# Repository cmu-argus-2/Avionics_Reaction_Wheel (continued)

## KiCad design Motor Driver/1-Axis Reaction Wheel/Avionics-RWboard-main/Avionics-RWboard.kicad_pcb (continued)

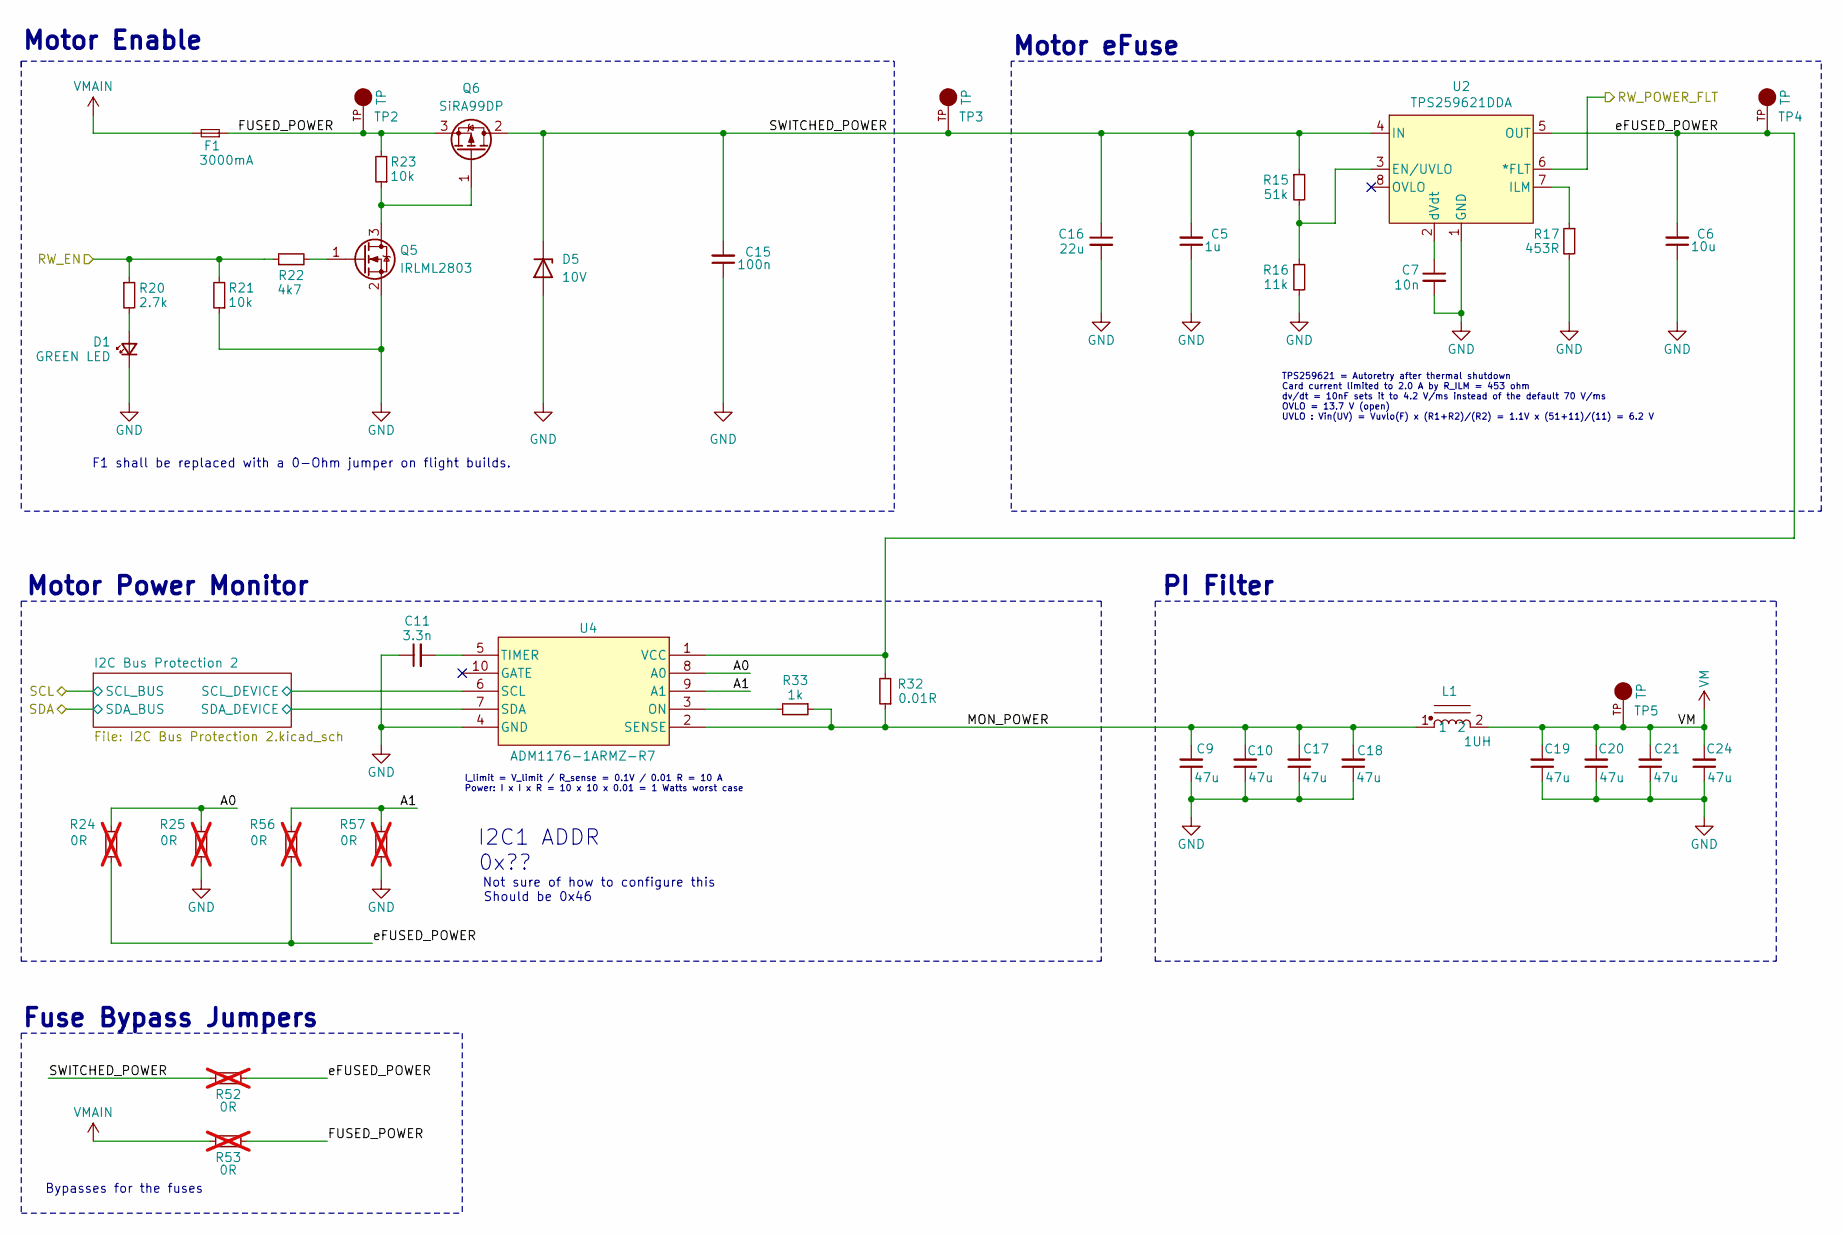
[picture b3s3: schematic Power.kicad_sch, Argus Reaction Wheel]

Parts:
C5: 1u; C_0603_1608Metric; Part CL10B105KA8NNNC; Digikey PN 1276-1184-1-ND
C6: 10u; C_1206_3216Metric_Pad1.33x1.80mm_HandSolder; Part CL31B106KAHNNNE; Digikey PN 1276-1804-1-ND
C7: 10n; C_0603_1608Metric; MPN CL10B103KO8WPNC; Digikey PN 490-4934-1-ND
C9, C10, C17, C18, C19, C20, C21, C24: 47u; C_1206_3216Metric_Pad1.33x1.80mm_HandSolder; Part C3216X5R1E476M160AC; Digikey PN 445-8047-1-ND
C11: 3.3n; C_0603_1608Metric; Part C0603C332K4REC7411; Digikey PN 399-C0603C332K4REC7411CT-ND
C15: 100n; C_0402_1005Metric_Pad0.74x0.62mm_HandSolder; Part C0402C103K3RACTU; Digikey PN 399-C0402C103K3RACTUCT-ND
C16: 22u; C_1210_3225Metric_Pad1.33x2.70mm_HandSolder; MPN GCM32EC71E226KE36K; Digikey PN 490-GCM32EC71E226KE36KCT-ND
D1: GREEN LED; LED_0603_1608Metric; MPN IN-S63AT5A; Digikey PN 1830-1064-1-ND
D5: 10V; Nexperia_DSN1608-2_1.6x0.8mm; MPN PTVS10VZ1USKYL; Digikey PN 1727-2744-1-ND
F1: 3000mA; Fuse_0603_1608Metric; Part SF-0603S300-2; Digikey PN SF-0603S300-2CT-ND
L1: 1UH; HCM1A1104V2; Part HCM1A1104V2-1R0-R; Digikey PN 283-HCM1A1104V2-1R0-RCT-ND
Q5: IRLML2803; SOT-23; MPN IRLML2803TRPBF; Digikey PN IRLML2803PBFCT-ND
Q6: SiRA99DP; PowerPAK SO-8; MPN SIRA99DP-T1-GE3; Digikey PN SIRA99DP-T1-GE3CT-ND
R15: 51k; R_0603_1608Metric; MPN RC0603FR-0751KL; Digikey PN 311-51.0KHRCT-ND
R16: 11k; R_0603_1608Metric; MPN RC0603FR-0711KL; Digikey PN 311-11.0KHRCT-ND
R17: 453R; R_0603_1608Metric; MPN RC0603FR-07453RL; Digikey PN 311-453HRCT-ND
R20: 2.7k; R_0603_1608Metric; MPN CRGCQ0603F2K7; Digikey PN A129693CT-ND
R21, R23: 10k; R_0603_1608Metric; MPN RC0603FR-0710KL; Digikey PN 311-10.0KHRCT-ND
R22: 4k7; R_0603_1608Metric; MPN RC0603FR-074K7L; Digikey PN 311-4.70KHRCT-ND
R24, R25, R56, R57: 0R; R_0402_1005Metric_Pad0.72x0.64mm_HandSolder; MPN RC0402JR-070RL; Digikey PN 311-0.0JRCT-ND; not fitted
R32: 0.01R; R_0805_2012Metric_Pad1.20x1.40mm_HandSolder; Part ERJ-8BWFR010V; Digikey PN P.010AUCT-ND
R33: 1k; R_0603_1608Metric; MPN RC0603FR-071KL; Digikey PN 311-1.00KHRCT-ND
R52, R53: 0R; R_2512_6332Metric_Pad1.40x3.35mm_HandSolder; Part RC2512FK-070RL; Digikey PN 13-RC2512FK-070RLCT-ND; not fitted
TP2, TP3, TP4, TP5: TP; KEYSTONE_5001; MPN 5001; Digikey PN 36-5001-ND
U2: TPS259621DDA; Texas_R-PDSO-G8_EP2.95x4.9mm_Mask2.4x3.1mm_ThermalVias; MPN TPS259620DDAT; Digikey PN 296-TPS259621DDARCT-ND
U4: ADM1176-1ARMZ-R7; MSOP-10_3x3mm_P0.5mm; Manufacturer_Part_Number ADM1176-1ARMZ-R7; Digikey PN 505-ADM1176-1ARMZ-R7CT-ND

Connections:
/Connectors/RW_EN: R20.1, R21.2, R22.1; also elsewhere on the board
/Connectors/RW_POWER_FLT: U2.6 (*FLT); also elsewhere on the board
/Power/A0: R24.2, R25.2, U4.8 (A0)
/Power/A1: R56.2, R57.2, U4.9 (A1)
/Power/FUSED_POWER: F1.1, Q6.3 (S), R23.2, R53.1, TP2.TP
/Power/I2C Bus Protection 2/SCL_DEVICE: U4.6 (SCL); also elsewhere on the board
/Power/I2C Bus Protection 2/SDA_DEVICE: U4.7 (SDA); also elsewhere on the board
/Power/MON_POWER: C9.2, C10.2, C17.2, C18.2, L1.1, R32.1, R33.1, U4.2 (SENSE)
/Power/SWITCHED_POWER: C5.2, C15.2, C16.1, D5.1 (K), Q6.2 (D), R15.1, R52.2, TP3.TP, U2.4 (IN)
/Power/eFUSED_POWER: C6.2, R24.1, R32.2, R52.1, R56.1, TP4.TP, U2.5 (OUT), U4.1 (VCC)
GND: C5.1, C6.1, C7.2, C9.1, C10.1, C11.1, C15.1, C16.2, C17.1, C18.1, C19.1, C20.1, C21.1, C24.1, D1.1 (K), D5.2 (A), Q5.2 (S), R16.2, R17.2, R21.1, R25.1, R57.1, U2.1 (GND), U2.9 (GND), U4.4 (GND); also elsewhere on the board
unnamed: D1.2 (A), R20.2
unnamed: Q5.3 (D), Q6.1 (G), R23.1
unnamed: Q5.1 (G), R22.2
unnamed: R15.2, R16.1, U2.3 (EN/UVLO)
unnamed: R17.1, U2.7 (ILM)
unnamed: C7.1, U2.2 (dVdt)
unnamed: R33.2, U4.3 (ON)
unnamed: C11.2, U4.5 (TIMER)
VM: C19.2, C20.2, C21.2, C24.2, L1.2, TP5.TP; also elsewhere on the board
VMAIN: F1.2, R53.2; also elsewhere on the board

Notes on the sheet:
Not sure of how to configure this
I2C1 ADDR
0x??
Motor Enable
F1 shall be replaced with a 0-Ohm jumper on flight builds.
I_limit = V_limit / R_sense = 0.1V / 0.01 R = 10 A Power: I x I x R = 10 x 10 x 0.01 = 1 Watts worst case
Motor Power Monitor
TPS259621 = Autoretry after thermal shutdown Card current limited to 2.0 A by R_ILM = 453 ohm dv/dt = 10nF sets it to 4.2 V/ms instead of the default 70 V/ms OVLO = 13.7 V (open) UVLO : Vin(UV) = Vuvlo(F) x (R1+R2)/(R2) = 1.1V x (51+11)/(11) = 6.2 V
Fuse Bypass Jumpers
Should be 0x46
PI Filter
Bypasses for the fuses
Motor eFuse

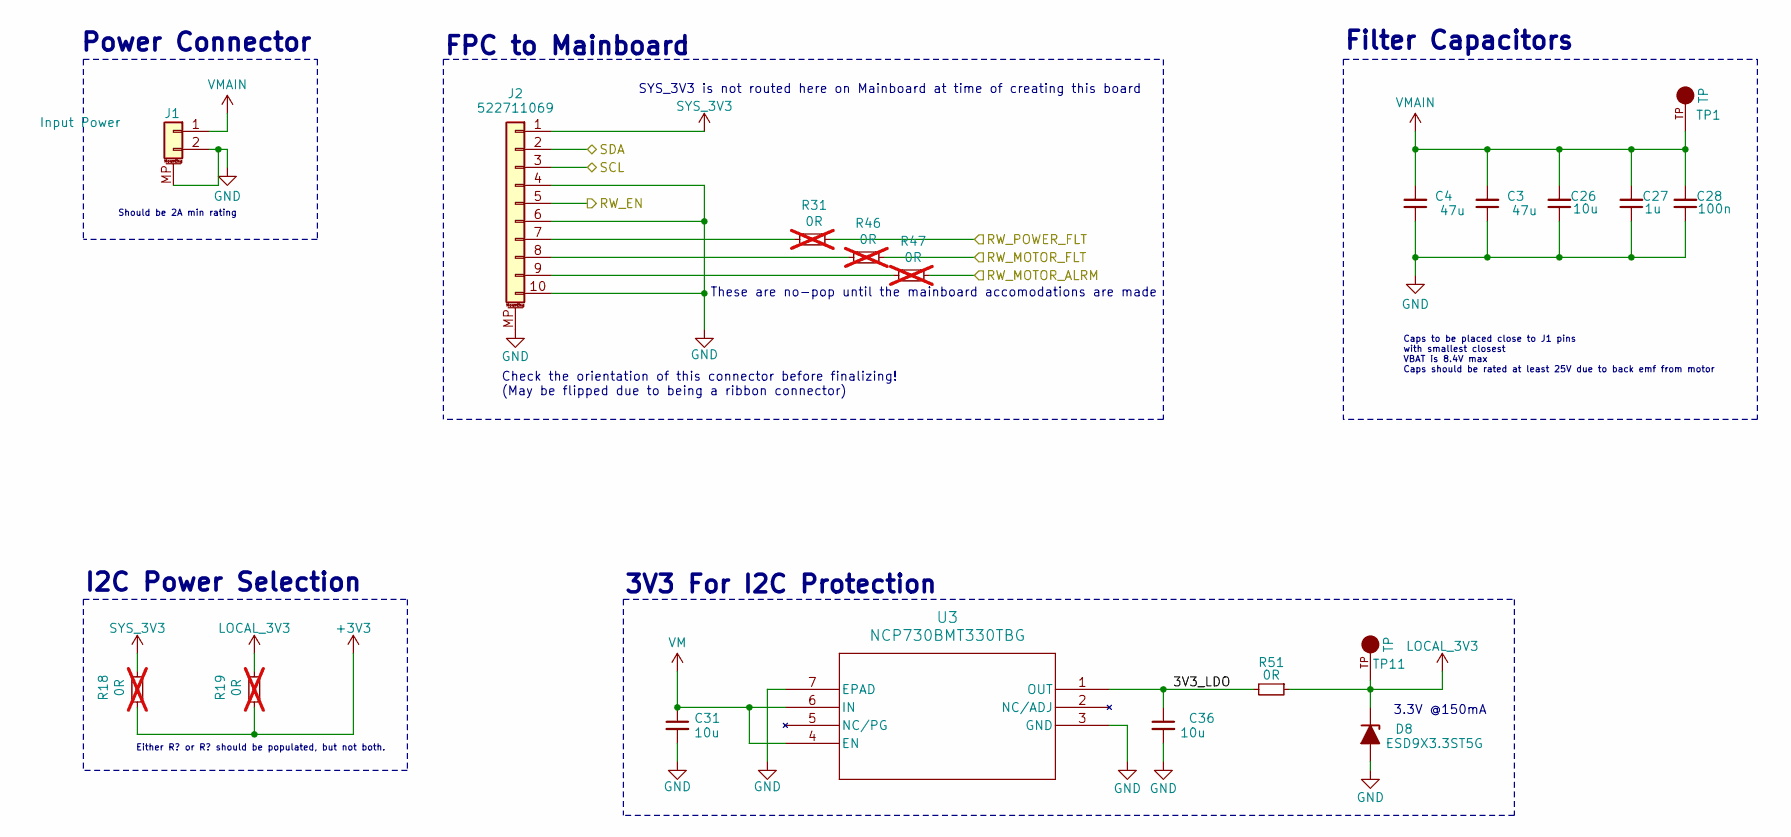
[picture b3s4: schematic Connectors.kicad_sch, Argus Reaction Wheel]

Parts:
C3, C4: 47u; C_1206_3216Metric_Pad1.33x1.80mm_HandSolder; Part C3216X5R1E476M160AC; Digikey PN 445-8047-1-ND
C26: 10u; C_1206_3216Metric_Pad1.33x1.80mm_HandSolder; Part CL31B106KAHNNNE; Digikey PN 1276-1804-1-ND
C27: 1u; C_0603_1608Metric; Part CL10B105KA8NNNC; Digikey PN 1276-1184-1-ND
C28: 100n; C_0402_1005Metric_Pad0.74x0.62mm_HandSolder; Part C0402C103K3RACTU; Digikey PN 399-C0402C103K3RACTUCT-ND
C31, C36: 10u; C_0603_1608Metric; MPN C1608X5R1E106M080AC; Digikey PN 445-9015-1-ND
D8: ESD9X3.3ST5G; D_SOD-923; MPN ESD9X5.0ST5G; Digikey PN ESD9X3.3ST5GOSCT-ND
J1: Input Power; Molex_Pico-Lock_504050-0291_1x02-1MP_P1.50mm_Horizontal
J2: 522711069; Molex_200528-0100_1x10-1MP_P1.00mm_Horizontal; MPN 200528-0100; Digikey PN 900-2005280100CT-ND
R18, R19, R31, R46, R47: 0R; R_0402_1005Metric_Pad0.72x0.64mm_HandSolder; MPN RC0402JR-070RL; Digikey PN 311-0.0JRCT-ND; not fitted
R51: 0R; R_0603_1608Metric; MPN CR0603-J/-000ELF; Digikey PN CR0603-J/-000ELFCT-ND
TP1, TP11: TP; KEYSTONE_5001; MPN 5001; Digikey PN 36-5001-ND
U3: NCP730BMT330TBG; WDFN6-2x2_511BR_OSI; MPN NCP730BMT330TBG; Digikey PN 488-NCP730BMT330TBGCT-ND

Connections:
+3V3: R18.1, R19.1; also elsewhere on the board
/Connectors/3V3_LDO: C36.1, R51.2, U3.1 (OUT)
/Connectors/RW_EN: J2.5; also elsewhere on the board
/Connectors/RW_MOTOR_ALRM: R47.2; also elsewhere on the board
/Connectors/RW_MOTOR_FLT: R46.2; also elsewhere on the board
/Connectors/RW_POWER_FLT: R31.2; also elsewhere on the board
/Connectors/SCL: J2.3; also elsewhere on the board
/Connectors/SDA: J2.2; also elsewhere on the board
GND: C3.1, C4.1, C26.1, C27.1, C28.1, C31.2, C36.2, D8.2 (A), J1.2, J1.MP (MountPin), J2.4, J2.6, J2.10, J2.MP (MountPin), U3.3 (GND), U3.7 (EPAD); also elsewhere on the board
LOCAL_3V3: D8.1 (K), R19.2, R51.1, TP11.TP
unnamed: J2.7, R31.1
unnamed: J2.8, R46.1
unnamed: J2.9, R47.1
SYS_3V3: J2.1, R18.2
VM: C31.1, U3.4 (EN), U3.6 (IN); also elsewhere on the board
VMAIN: C3.2, C4.2, C26.2, C27.2, C28.2, J1.1, TP1.TP; also elsewhere on the board

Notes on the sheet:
Filter Capacitors
Caps to be placed close to J1 pins with smallest closest VBAT is 8.4V max Caps should be rated at least 25V due to back emf from motor
3.3V @150mA
These are no-pop until the mainboard accomodations are made
Check the orientation of this connector before finalizing! (May be flipped due to being a ribbon connector)
Either R? or R? should be populated, but not both.
3V3 For I2C Protection
Should be 2A min rating
I2C Power Selection
SYS_3V3 is not routed here on Mainboard at time of creating this board
Power Connector
FPC to Mainboard

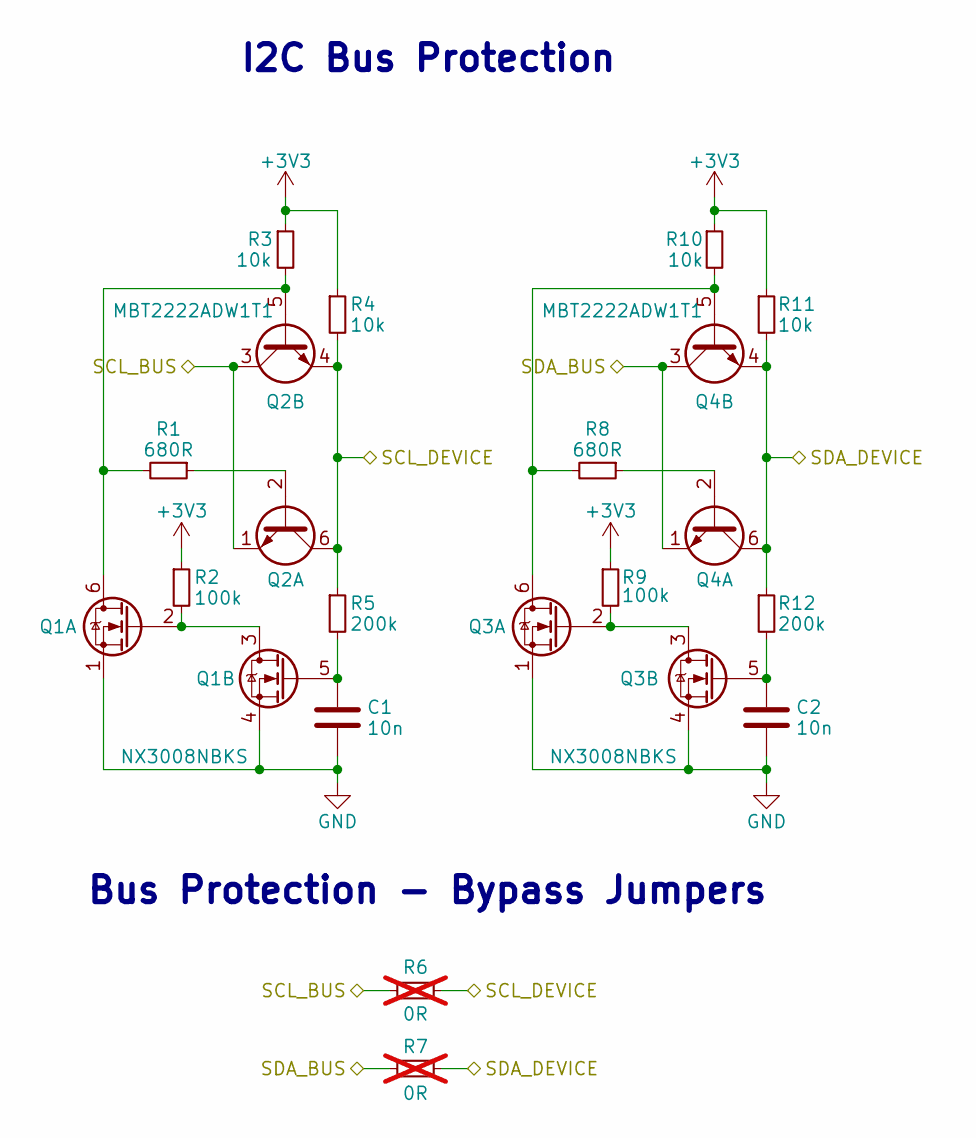
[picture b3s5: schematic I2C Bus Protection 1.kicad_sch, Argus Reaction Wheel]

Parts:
C1, C2: 10n; C_0603_1608Metric; Part CL10B103KO8WPNC; Digikey PN 490-4934-1-ND
Q1, Q3: NX3008NBKS; SOT-363_SC-70-6; Manufacturer_Part_Number NX3008NBKS; Digikey PN 1727-1221-1-ND
Q2, Q4: MBT2222ADW1T1; SOT-363_SC-70-6; Manufacturer_Part_Number MBT2222ADW1T1G; Digikey PN MBT2222ADW1T1GOSCT-ND
R1, R8: 680R; R_0603_1608Metric; MPN RC0603FR-07680RL; Digikey PN 311-680HRCT-ND
R2, R9: 100k; R_0603_1608Metric; MPN RC0603FR-07100KL; Digikey PN 311-100KHRCT-ND
R3, R4, R10, R11: 10k; R_0603_1608Metric; MPN RC0603FR-0710KL; Digikey PN 311-10.0KHRCT-ND
R5, R12: 200k; R_0603_1608Metric; MPN RC0603FR-07200KL; Digikey PN 311-200KHRCT-ND
R6, R7: 0R; R_0603_1608Metric; MPN CR0603-J/-000ELF; Digikey PN CR0603-J/-000ELFCT-ND; not fitted

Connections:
+3V3: R2.1, R3.1, R4.1, R9.1, R10.1, R11.1; also elsewhere on the board
/Connectors/SCL: Q2.1 (E1), Q2.3 (C2), R6.2; also elsewhere on the board
/Connectors/SDA: Q4.1 (E1), Q4.3 (C2), R7.2; also elsewhere on the board
/Motor/I2C Bus Protection 1/SCL_DEVICE: Q2.4 (E2), Q2.6 (C1), R4.2, R5.1, R6.1; also elsewhere on the board
/Motor/I2C Bus Protection 1/SDA_DEVICE: Q4.4 (E2), Q4.6 (C1), R7.1, R11.2, R12.1; also elsewhere on the board
GND: C1.2, C2.2, Q1.1 (S), Q1.4 (S), Q3.1 (S), Q3.4 (S); also elsewhere on the board
unnamed: Q1.6 (D), Q2.5 (B2), R1.2, R3.2
unnamed: Q1.2 (G), Q1.3 (D), R2.2
unnamed: C1.1, Q1.5 (G), R5.2
unnamed: Q2.2 (B1), R1.1
unnamed: Q3.6 (D), Q4.5 (B2), R8.2, R10.2
unnamed: Q3.2 (G), Q3.3 (D), R9.2
unnamed: C2.1, Q3.5 (G), R12.2
unnamed: Q4.2 (B1), R8.1

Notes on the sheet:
Bus Protection - Bypass Jumpers
I2C Bus Protection

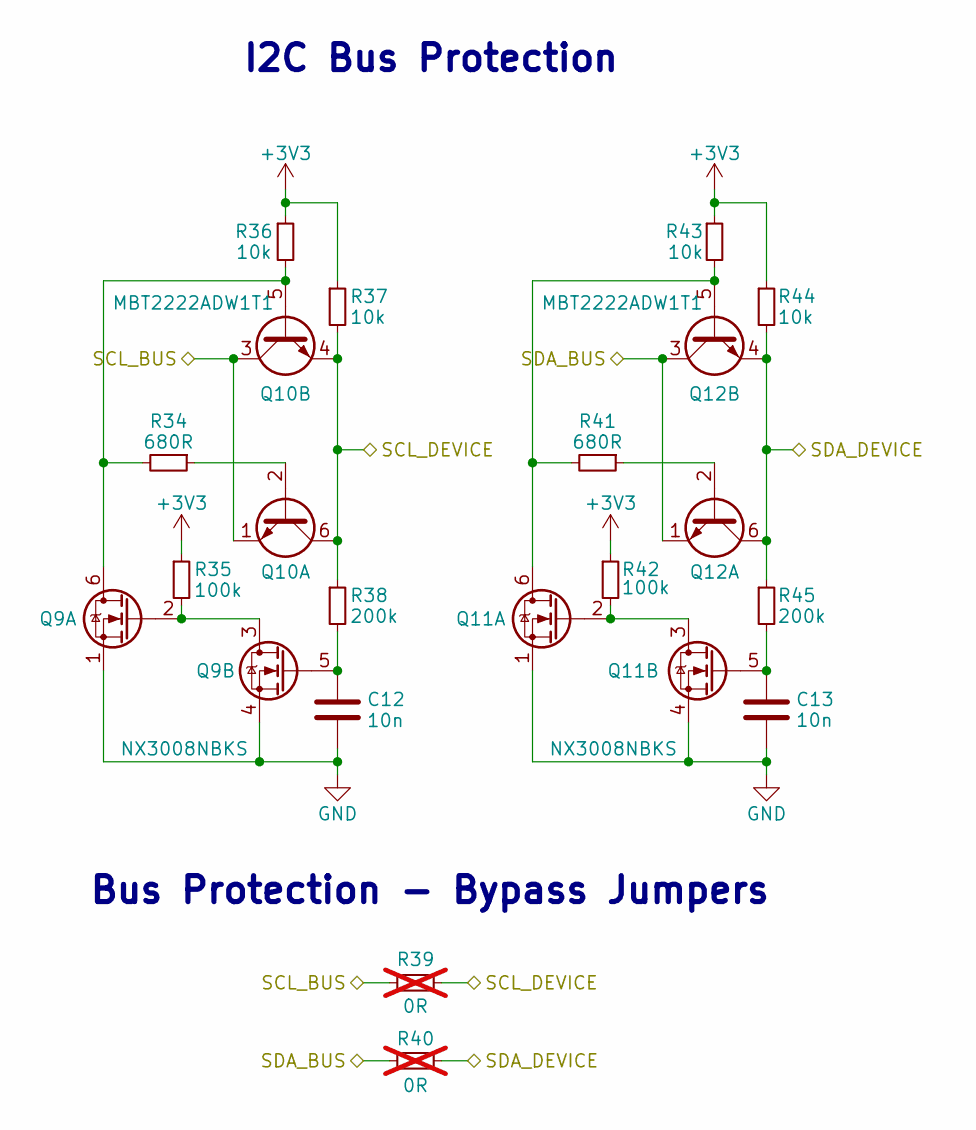
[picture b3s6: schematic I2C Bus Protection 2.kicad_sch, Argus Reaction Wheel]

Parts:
C12, C13: 10n; C_0603_1608Metric; Part CL10B103KO8WPNC; Digikey PN 490-4934-1-ND
Q9, Q11: NX3008NBKS; SOT-363_SC-70-6; Manufacturer_Part_Number NX3008NBKS; Digikey PN 1727-1221-1-ND
Q10, Q12: MBT2222ADW1T1; SOT-363_SC-70-6; Manufacturer_Part_Number MBT2222ADW1T1G; Digikey PN MBT2222ADW1T1GOSCT-ND
R34, R41: 680R; R_0603_1608Metric; MPN RC0603FR-07680RL; Digikey PN 311-680HRCT-ND
R35, R42: 100k; R_0603_1608Metric; MPN RC0603FR-07100KL; Digikey PN 311-100KHRCT-ND
R36, R37, R43, R44: 10k; R_0603_1608Metric; MPN RC0603FR-0710KL; Digikey PN 311-10.0KHRCT-ND
R38, R45: 200k; R_0603_1608Metric; MPN RC0603FR-07200KL; Digikey PN 311-200KHRCT-ND
R39, R40: 0R; R_0603_1608Metric; MPN CR0603-J/-000ELF; Digikey PN CR0603-J/-000ELFCT-ND; not fitted

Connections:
+3V3: R35.1, R36.1, R37.1, R42.1, R43.1, R44.1; also elsewhere on the board
/Connectors/SCL: Q10.1 (E1), Q10.3 (C2), R39.2; also elsewhere on the board
/Connectors/SDA: Q12.1 (E1), Q12.3 (C2), R40.2; also elsewhere on the board
/Power/I2C Bus Protection 2/SCL_DEVICE: Q10.4 (E2), Q10.6 (C1), R37.2, R38.1, R39.1; also elsewhere on the board
/Power/I2C Bus Protection 2/SDA_DEVICE: Q12.4 (E2), Q12.6 (C1), R40.1, R44.2, R45.1; also elsewhere on the board
GND: C12.2, C13.2, Q9.1 (S), Q9.4 (S), Q11.1 (S), Q11.4 (S); also elsewhere on the board
unnamed: Q9.2 (G), Q9.3 (D), R35.2
unnamed: C12.1, Q9.5 (G), R38.2
unnamed: Q10.2 (B1), R34.1
unnamed: Q9.6 (D), Q10.5 (B2), R34.2, R36.2
unnamed: Q11.6 (D), Q12.5 (B2), R41.2, R43.2
unnamed: Q11.2 (G), Q11.3 (D), R42.2
unnamed: C13.1, Q11.5 (G), R45.2
unnamed: Q12.2 (B1), R41.1

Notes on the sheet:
Bus Protection - Bypass Jumpers
I2C Bus Protection

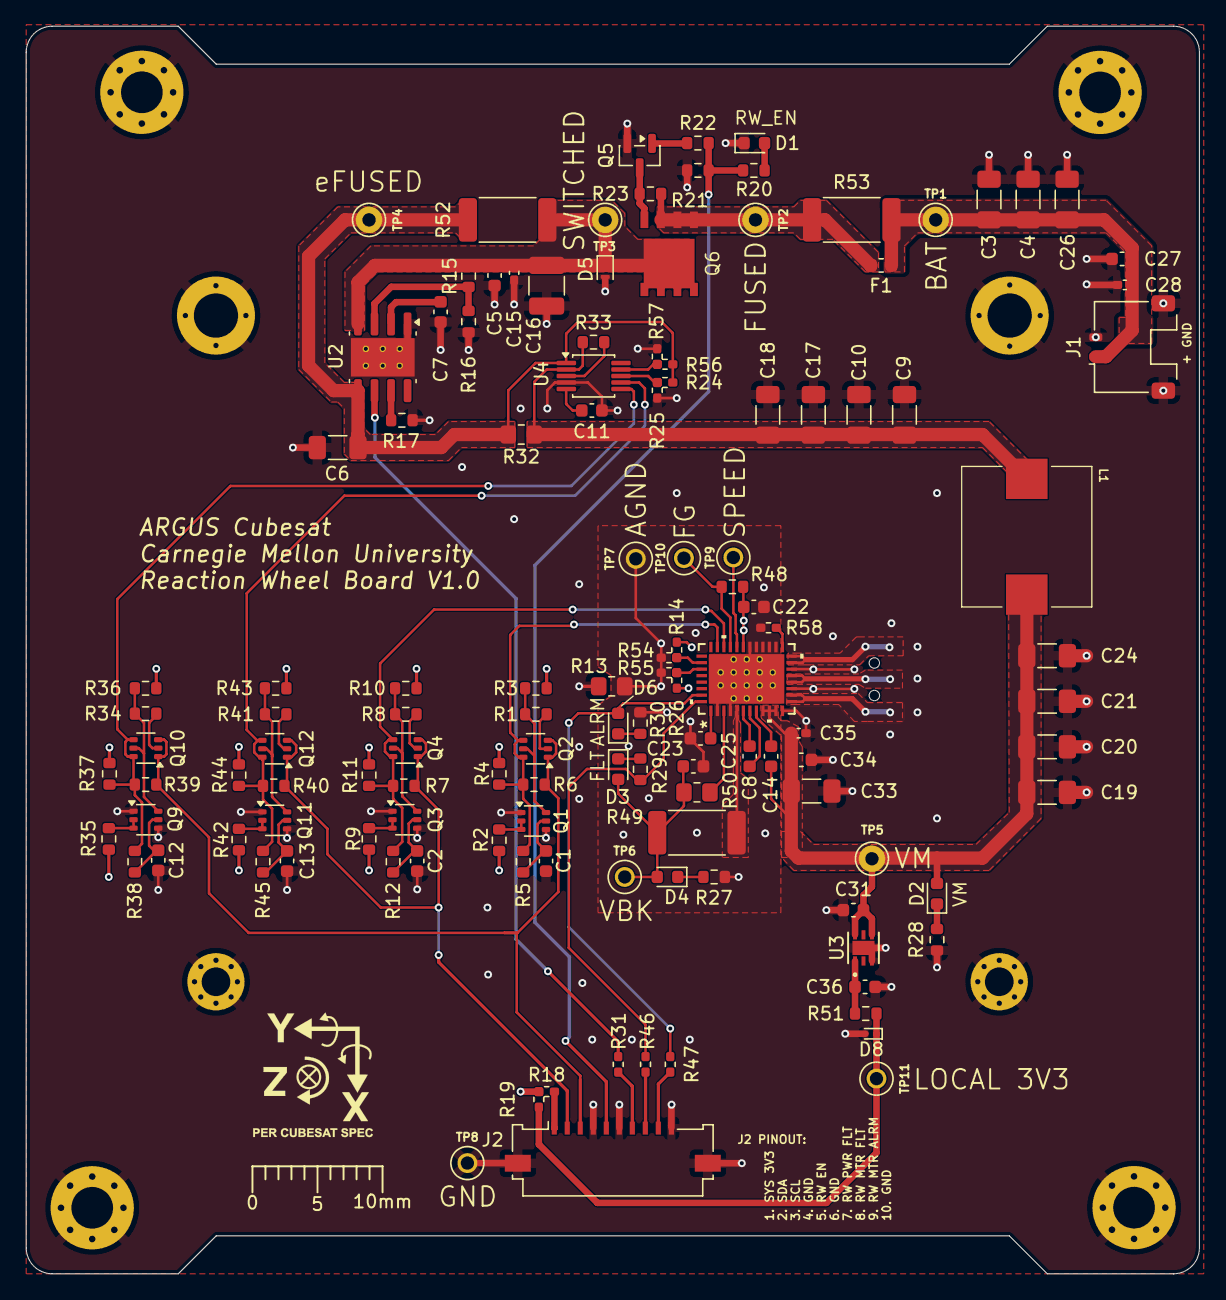
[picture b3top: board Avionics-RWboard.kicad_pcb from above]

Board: 4 copper layers, 90.2 x 95.9 mm, 132 parts (1 on the bottom side), 71 nets.

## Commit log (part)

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2026-06-22 I2C scan
2026-06-22 added reaction wheel testing
2026-06-22 removed unused config code
2026-06-23 direction setting works cw and ccw
2026-06-23 read register function added, works.
2026-06-25 as5600 encoder magnet detect test - pass (hardware related)
2026-06-25 dedicated magnet detect fn
2026-06-29 reading rpm from HALL sensor i think
2026-06-29 cleaned up and added documentation
2026-06-29 officially done getting one motor moving and reading rpm yippee
